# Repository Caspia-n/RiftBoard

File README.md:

<h1>My Project</h1>
RiftBoard is a comprehensive devboard built around the RP2040 chipset, it features a very fancy (and time consuming) ground fill, some 3v3 and some VBUS, also lots of GND. I built it mainly for testing and using sensors and actuators, either on their own or working together.
<h1>Why?</h1>
I started this project because I wanted to get into hardware design and embedded electronics. But also because I love HackClub and what they do and really wanted to be a part of this, I thank you so much for the opportunities, and I also really want a hot plate for future projects :).

<h1>Pics</h1>

<h1>BOM</h1>
<table>
    <tr>
        <td>Mrf#</td>
        <td>Mfr.</td>
        <td>Order Qty.</td>
        <td>Unit Price(USD)</td>
        <td>Ext.Price(USD)</td>
        <td>LCSC#</td>
        <td>Package</td>
        <td>Min</td>
        <td>Mult</td>
        <td>SPQ</td>
        <td>Availability</td>
        <td>Stock Status</td>
        <td>Customer Notes</td>
        <td>Description</td>
        <td>Purpose</td>
        <td>Product Link</td>
    </tr>
    <tr>
        <td>CC0402KRX7R7BB104</td>
        <td>YAGEO</td>
        <td>100</td>
        <td>0.0010</td>
        <td>0.10</td>
        <td>C60474</td>
        <td>0402</td>
        <td>100</td>
        <td>100</td>
        <td>10000</td>
        <td>11898300</td>
        <td>In Stock</td>
        <td></td>
        <td>100nF ±10% 16V Ceramic Capacitor X7R 0402</td>
        <td>Capacitors for decoupling and stabilisation of powerlines</td>
        <td>https://www.lcsc.com/product-detail/C60474.html</td>
    </tr>
    <tr>
        <td>CL05A105KP5NNNC</td>
        <td>Samsung Electro-Mechanics</td>
        <td>100</td>
        <td>0.0023</td>
        <td>0.23</td>
        <td>C14445</td>
        <td>0402</td>
        <td>100</td>
        <td>100</td>
        <td>10000</td>
        <td>1500800</td>
        <td>In Stock</td>
        <td></td>
        <td>1uF ±10% 10V Ceramic Capacitor X5R 0402</td>
        <td>One for each power line</td>
        <td>https://www.lcsc.com/product-detail/C14445.html</td>
    </tr>
    <tr>
        <td>CL10A106KP8NNNC</td>
        <td>Samsung Electro-Mechanics</td>
        <td>50</td>
        <td>0.0080</td>
        <td>0.40</td>
        <td>C19702</td>
        <td>0603</td>
        <td>50</td>
        <td>50</td>
        <td>4000</td>
        <td>3665250</td>
        <td>In Stock</td>
        <td></td>
        <td>10uF ±10% 10V Ceramic Capacitor X5R 0603</td>
        <td>Caps for the stepdown converter</td>
        <td>https://www.lcsc.com/product-detail/C19702.html</td>
    </tr>
    <tr>
        <td>CL05C330JB5NNNC</td>
        <td>Samsung Electro-Mechanics</td>
        <td>100</td>
        <td>0.0036</td>
        <td>0.36</td>
        <td>C70465</td>
        <td>0402</td>
        <td>100</td>
        <td>100</td>
        <td>10000</td>
        <td>209500</td>
        <td>In Stock</td>
        <td></td>
        <td>33pF ±5% 50V Ceramic Capacitor C0G 0402</td>
        <td>Caps for the crystal</td>
        <td>https://www.lcsc.com/product-detail/C70465.html</td>
    </tr>
    <tr>
        <td>YLED0603B</td>
        <td>YONGYUTAI</td>
        <td>100</td>
        <td>0.0060</td>
        <td>0.60</td>
        <td>C19171394</td>
        <td>0603</td>
        <td>100</td>
        <td>100</td>
        <td>4000</td>
        <td>55000</td>
        <td>In Stock</td>
        <td></td>
        <td>Blue LED Indication - Discrete 2.6V~3.2V 0603</td>
        <td>Blue programmable LED</td>
        <td>https://www.lcsc.com/product-detail/C19171394.html</td>
    </tr>
    <tr>
        <td>YLED0603R</td>
        <td>YONGYUTAI</td>
        <td>100</td>
        <td>0.0061</td>
        <td>0.61</td>
        <td>C19171390</td>
        <td>0603</td>
        <td>100</td>
        <td>100</td>
        <td>4000</td>
        <td>267100</td>
        <td>In Stock</td>
        <td></td>
        <td>Red LED Indication - Discrete 1.8V~2.4V 0603</td>
        <td>Red programmable LED</td>
        <td>https://www.lcsc.com/product-detail/C19171390.html</td>
    </tr>
    <tr>
        <td>HX TYPE-C 16PIN</td>
        <td>hanxia</td>
        <td>5</td>
        <td>0.0704</td>
        <td>0.35</td>
        <td>C5178539</td>
        <td>SMD</td>
        <td>5</td>
        <td>5</td>
        <td>1000</td>
        <td>34690</td>
        <td>In Stock</td>
        <td></td>
        <td>USB-C (USB TYPE-C) Receptacle Connector 16 Position Surface Mount, Right Angle</td>
        <td>Usb interface</td>
        <td>https://www.lcsc.com/product-detail/C5178539.html</td>
    </tr>
    <tr>
        <td>PH2.54-1X20P-H25</td>
        <td>JXTCONN</td>
        <td>10</td>
        <td>0.0920</td>
        <td>0.92</td>
        <td>C42431804</td>
        <td>Through Hole,P=2.54mm</td>
        <td>5</td>
        <td>5</td>
        <td>200</td>
        <td>9870</td>
        <td>In Stock</td>
        <td></td>
        <td>Pin Header 20 Position 2.54mm Pitch Single Row Through Hole -40℃~+105℃</td>
        <td>Main Pin headers</td>
        <td>https://www.lcsc.com/product-detail/C42431804.html</td>
    </tr>
    <tr>
        <td>HX PH254-01-03-Z-L11.5 pcb pin header</td>
        <td>hanxia</td>
        <td>20</td>
        <td>0.0192</td>
        <td>0.38</td>
        <td>C52016391</td>
        <td>Through Hole,P=2.54mm</td>
        <td>20</td>
        <td>20</td>
        <td>2000</td>
        <td>9760</td>
        <td>In Stock</td>
        <td></td>
        <td>Pin Header 1 2.5mm 6mm 3P -40℃~+105℃ 3mm 2.54mm 3A 1kV 1x3P Through Hole,P=2.54mm Headers, Male Pins RoHS</td>
        <td>3pin-connector</td>
        <td>https://www.lcsc.com/product-detail/C52016391.html</td>
    </tr>
    <tr>
        <td>RC0402FR-075K1L</td>
        <td>YAGEO</td>
        <td>100</td>
        <td>0.0009</td>
        <td>0.09</td>
        <td>C105872</td>
        <td>0402</td>
        <td>100</td>
        <td>100</td>
        <td>10000</td>
        <td>1024700</td>
        <td>In Stock</td>
        <td></td>
        <td>5.1kΩ 62.5mW 50V Thick Film Resistor ±100ppm/℃ ±1% 0402 Chip Resistor - Surface Mount RoHS</td>
        <td>Pull-down resistors for CC1/2 on usb interface</td>
        <td>https://www.lcsc.com/product-detail/C105872.html</td>
    </tr>
    <tr>
        <td>FRC0402F27R0TS</td>
        <td>FOJAN</td>
        <td>100</td>
        <td>0.0006</td>
        <td>0.06</td>
        <td>C2909343</td>
        <td>0402</td>
        <td>100</td>
        <td>100</td>
        <td>10000</td>
        <td>443300</td>
        <td>In Stock</td>
        <td></td>
        <td>27Ω ±1% 62.5mW 0402 Thick Film Resistor</td>
        <td>Resistors for the differential pair to usb interface</td>
        <td>https://www.lcsc.com/product-detail/C2909343.html</td>
    </tr>
    <tr>
        <td>RC0402FR-071KL</td>
        <td>YAGEO</td>
        <td>100</td>
        <td>0.0008</td>
        <td>0.08</td>
        <td>C106235</td>
        <td>0402</td>
        <td>100</td>
        <td>100</td>
        <td>10000</td>
        <td>5051800</td>
        <td>In Stock</td>
        <td></td>
        <td>1kΩ 62.5mW 50V Thick Film Resistor ±100ppm/℃ ±1% 0402 Chip Resistor - Surface Mount RoHS</td>
        <td>One for the crystal and one for flash mem</td>
        <td>https://www.lcsc.com/product-detail/C106235.html</td>
    </tr>
    <tr>
        <td>RC0402FR-0710KL</td>
        <td>YAGEO</td>
        <td>100</td>
        <td>0.0008</td>
        <td>0.08</td>
        <td>C60490</td>
        <td>0402</td>
        <td>100</td>
        <td>100</td>
        <td>10000</td>
        <td>1433400</td>
        <td>In Stock</td>
        <td></td>
        <td>62.5mW 10kΩ 50V Thick Film Resistor ±100ppm/℃ ±1% 0402 Chip Resistor - Surface Mount RoHS</td>
        <td>Flash mem to power resistor</td>
        <td>https://www.lcsc.com/product-detail/C60490.html</td>
    </tr>
    <tr>
        <td>FRC0402F50R0TS</td>
        <td>FOJAN</td>
        <td>100</td>
        <td>0.0006</td>
        <td>0.06</td>
        <td>C51048227</td>
        <td>0402</td>
        <td>100</td>
        <td>100</td>
        <td>10000</td>
        <td>495800</td>
        <td>In Stock</td>
        <td></td>
        <td>62.5mW 50Ω 50V Thick Film Resistor ±100ppm/℃ ±1% 0402 Chip Resistor - Surface Mount RoHS</td>
        <td>50R resistor for Red LED</td>
        <td>https://www.lcsc.com/product-detail/C51048227.html</td>
    </tr>
    <tr>
        <td>0603WAF100JT5E</td>
        <td>UNI-ROYAL</td>
        <td>20</td>
        <td>0.0017</td>
        <td>0.03</td>
        <td>C22859</td>
        <td>0603</td>
        <td>20</td>
        <td>20</td>
        <td>5000</td>
        <td>158680</td>
        <td>In Stock</td>
        <td></td>
        <td>10Ω ±1% 100mW 0603 Thick Film Resistor</td>
        <td>10R resistor for Blue LED</td>
        <td>https://www.lcsc.com/product-detail/C22859.html</td>
    </tr>
    <tr>
        <td>TS-1088-AR02016</td>
        <td>XUNPU</td>
        <td>10</td>
        <td>0.0545</td>
        <td>0.55</td>
        <td>C720477</td>
        <td>SMD,4x3mm</td>
        <td>10</td>
        <td>10</td>
        <td>4000</td>
        <td>376970</td>
        <td>In Stock</td>
        <td></td>
        <td>Tactile Switch SPST 160gf 2mm SMD (SMT) Tab 4mm x 3mm Surface Mount</td>
        <td>One switch for flash write mode, and one programmable.</td>
        <td>https://www.lcsc.com/product-detail/C720477.html</td>
    </tr>
    <tr>
        <td>RP2040</td>
        <td>Raspberry Pi</td>
        <td>5</td>
        <td>0.9482</td>
        <td>4.74</td>
        <td>C2040</td>
        <td>LQFN-56(7x7)</td>
        <td>1</td>
        <td>1</td>
        <td>3400</td>
        <td>101373</td>
        <td>In Stock</td>
        <td></td>
        <td>133MHz 30 LQFN-56(7x7) Microcontrollers RoHS</td>
        <td>The MCU on this board</td>
        <td>https://www.lcsc.com/product-detail/C2040.html</td>
    </tr>
    <tr>
        <td>MCP1700T-3302E/TT</td>
        <td>MICROCHIP</td>
        <td>5</td>
        <td>0.3762</td>
        <td>1.88</td>
        <td>C39051</td>
        <td>SOT-23</td>
        <td>5</td>
        <td>5</td>
        <td>3000</td>
        <td>9370</td>
        <td>In Stock</td>
        <td></td>
        <td>3.3V Positive Fixed SOT-23 Voltage Regulators - Linear, Low Drop Out (LDO) Regulators RoHS</td>
        <td>The stepdown converter from 5v to 3v3</td>
        <td>https://www.lcsc.com/product-detail/C39051.html</td>
    </tr>
    <tr>
        <td>W25Q16JVUXIQ</td>
        <td>Winbond</td>
        <td>10</td>
        <td>1.0529</td>
        <td>10.53</td>
        <td>C2843335</td>
        <td>USON-8-EP(2x3)</td>
        <td>10</td>
        <td>10</td>
        <td>4000</td>
        <td>34380</td>
        <td>In Stock</td>
        <td></td>
        <td>2.7V~3.6V 16Mbit 133MHz SPI USON-8-EP(2x3) Memory (ICs) RoHS</td>
        <td>The flash memory module</td>
        <td>https://www.lcsc.com/product-detail/C2843335.html</td>
    </tr>
    <tr>
        <td>X322512MSB4SI</td>
        <td>YXC Crystal Oscillators</td>
        <td>10</td>
        <td>0.0734</td>
        <td>0.73</td>
        <td>C9002</td>
        <td>SMD3225-4P</td>
        <td>10</td>
        <td>10</td>
        <td>3000</td>
        <td>436800</td>
        <td>In Stock</td>
        <td></td>
        <td>Crystal 12MHz ±10ppm 20pF SMD3225-4P</td>
        <td>the Crystal oscilator</td>
        <td>https://www.lcsc.com/product-detail/C9002.html</td>
    </tr>
</table>

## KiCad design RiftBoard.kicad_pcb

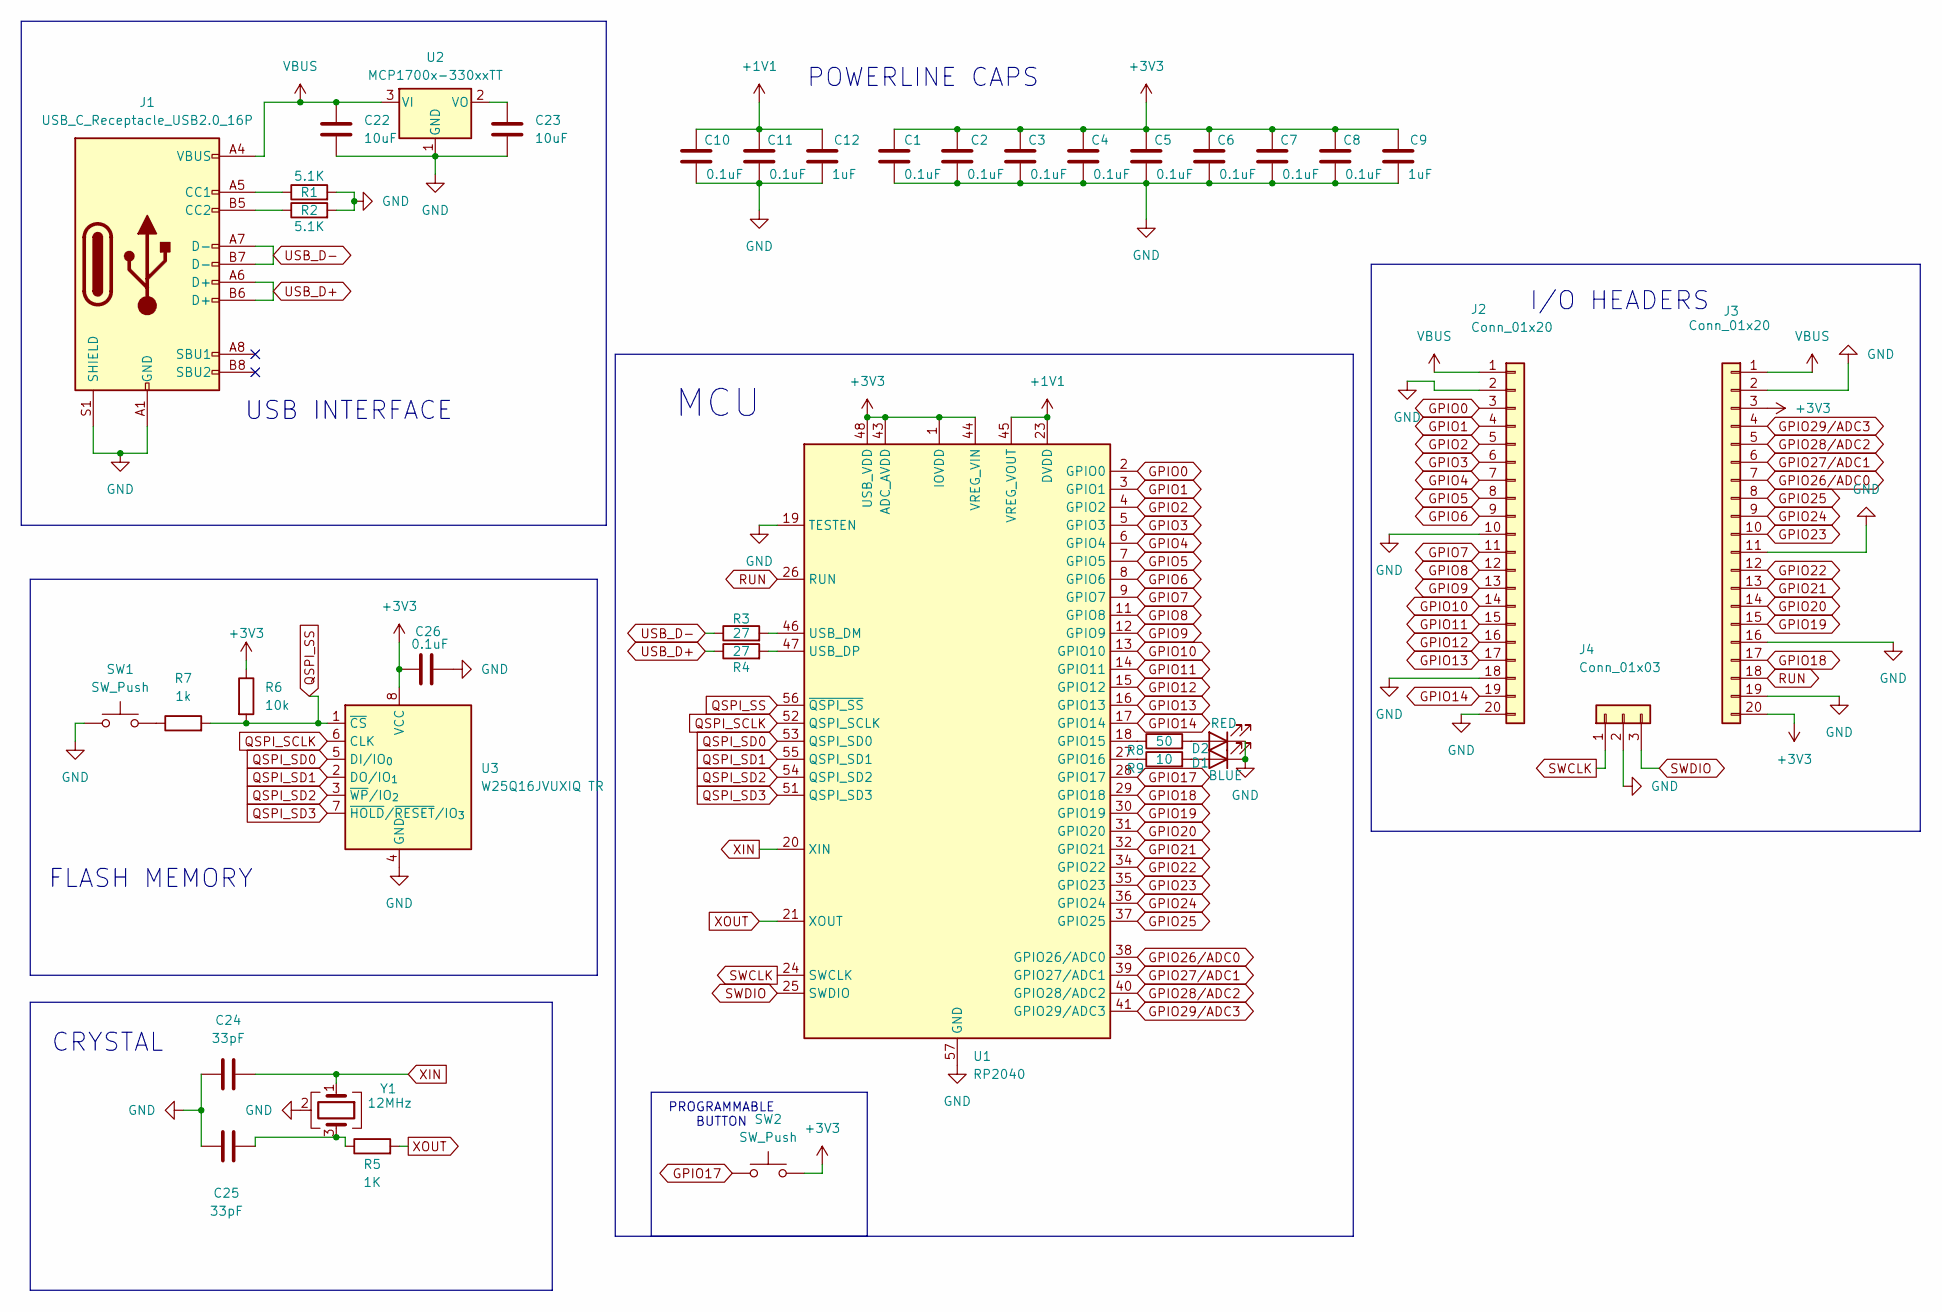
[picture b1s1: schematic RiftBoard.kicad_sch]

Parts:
C1, C2, C3, C4, C5, C6, C7, C8, C10, C11, C26: 0.1uF; C_0402_1005Metric
C9, C12: 1uF; C_0402_1005Metric
C22, C23: 10uF; C_0603_1608Metric
C24, C25: 33pF; C_0402_1005Metric
D1: BLUE; LED_0603_1608Metric
D2: RED; LED_0603_1608Metric
J1: USB_C_Receptacle_USB2.0_16P; USB_C_Receptacle_HRO_TYPE-C-31-M-12
J2, J3: Conn_01x20; PinHeader_1x20_P2.54mm_Vertical
J4: Conn_01x03; PinHeader_1x03_P2.54mm_Vertical
R1, R2: 5.1K; R_0402_1005Metric
R3, R4: 27; R_0402_1005Metric
R5: 1K; R_0402_1005Metric
R6: 10k; R_0402_1005Metric
R7: 1k; R_0402_1005Metric
R8: 50; R_0402_1005Metric
R9: 10; R_0402_1005Metric
SW1, SW2: SW_Push; SW_Push_SPST_NO_Alps_SKRK
U1: RP2040; QFN-56-1EP_7x7mm_P0.4mm_EP3.2x3.2mm
U2: MCP1700x-330xxTT; SOT-23
U3: W25Q16JVUXIQ TR; Winbond_USON-8-1EP_3x2mm_P0.5mm_EP0.2x1.6mm
Y1: 12MHz; Crystal_SMD_3225-4Pin_3.2x2.5mm

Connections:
+1V1: C10.1, C11.1, C12.1, U1.23 (DVDD), U1.45 (VREG_VOUT), U1.50 (DVDD)
+3V3: C1.1, C2.1, C3.1, C4.1, C5.1, C6.1, C7.1, C8.1, C9.1, C26.1, J3.3, J3.20, R6.1, SW2.2, U1.1 (IOVDD), U1.10 (IOVDD), U1.22 (IOVDD), U1.33 (IOVDD), U1.42 (IOVDD), U1.43 (ADC_AVDD), U1.44 (VREG_VIN), U1.48 (USB_VDD), U1.49 (IOVDD), U3.8 (VCC)
GND: C1.2, C2.2, C3.2, C4.2, C5.2, C6.2, C7.2, C8.2, C9.2, C10.2, C11.2, C12.2, C22.2, C23.2, C24.1, C25.1, C26.2, D1.1 (K), D2.1 (K), J1.A1 (GND), J1.A12 (GND), J1.B1 (GND), J1.B12 (GND), J1.S1 (SHIELD), J1.SH (SHIELD), J2.2, J2.10, J2.18, J2.20, J3.2, J3.11, J3.16, J3.19, J4.2, R1.2, R2.2, SW1.1, U1.19 (TESTEN), U1.57 (GND), U2.1 (GND), U3.4 (GND), Y1.2 (G), Y1.4 (G)
GPIO0: J2.3, U1.2 (GPIO0)
GPIO1: J2.4, U1.3 (GPIO1)
GPIO2: J2.5, U1.4 (GPIO2)
GPIO3: J2.6, U1.5 (GPIO3)
GPIO4: J2.7, U1.6 (GPIO4)
GPIO5: J2.8, U1.7 (GPIO5)
GPIO6: J2.9, U1.8 (GPIO6)
GPIO7: J2.11, U1.9 (GPIO7)
GPIO8: J2.12, U1.11 (GPIO8)
GPIO9: J2.13, U1.12 (GPIO9)
GPIO10: J2.14, U1.13 (GPIO10)
GPIO11: J2.15, U1.14 (GPIO11)
GPIO12: J2.16, U1.15 (GPIO12)
GPIO13: J2.17, U1.16 (GPIO13)
GPIO14: J2.19, U1.17 (GPIO14)
GPIO17: SW2.1, U1.28 (GPIO17)
GPIO18: J3.17, U1.29 (GPIO18)
GPIO19: J3.15, U1.30 (GPIO19)
GPIO20: J3.14, U1.31 (GPIO20)
GPIO21: J3.13, U1.32 (GPIO21)
GPIO22: J3.12, U1.34 (GPIO22)
GPIO23: J3.10, U1.35 (GPIO23)
GPIO24: J3.9, U1.36 (GPIO24)
GPIO25: J3.8, U1.37 (GPIO25)
GPIO26/ADC0: J3.7, U1.38 (GPIO26/ADC0)
GPIO27/ADC1: J3.6, U1.39 (GPIO27/ADC1)
GPIO28/ADC2: J3.5, U1.40 (GPIO28/ADC2)
GPIO29/ADC3: J3.4, U1.41 (GPIO29/ADC3)
unnamed: C25.2, R5.1, Y1.3
unnamed: D1.2 (A), R9.2
unnamed: D2.2 (A), R8.2
unnamed: J1.A5 (CC1), R1.1
unnamed: J1.B5 (CC2), R2.1
unnamed: R7.1, SW1.2
unnamed: R8.1, U1.18 (GPIO15)
unnamed: R9.1, U1.27 (GPIO16)
unnamed: R3.2, U1.46 (USB_DM)
unnamed: R4.2, U1.47 (USB_DP)
unnamed: C23.1, U2.2 (VO)
QSPI_SCLK: U1.52 (QSPI_SCLK), U3.6 (CLK)
QSPI_SD0: U1.53 (QSPI_SD0), U3.5 (DI/IO_{0})
QSPI_SD1: U1.55 (QSPI_SD1), U3.2 (DO/IO_{1})
QSPI_SD2: U1.54 (QSPI_SD2), U3.3 (~WP/IO_{2})
QSPI_SD3: U1.51 (QSPI_SD3), U3.7 (~HOLD/~RESET/IO_{3})
QSPI_SS: R6.2, R7.2, U1.56 (~QSPI_SS), U3.1 (~CS)
RUN: J3.18, U1.26 (RUN)
SWCLK: J4.1, U1.24 (SWCLK)
SWDIO: J4.3, U1.25 (SWDIO)
USB_D+: J1.A6 (D+), J1.B6 (D+), R4.1
USB_D-: J1.A7 (D-), J1.B7 (D-), R3.1
VBUS: C22.1, J1.A4 (VBUS), J1.A9 (VBUS), J1.B4 (VBUS), J1.B9 (VBUS), J2.1, J3.1, U2.3 (VI)
XIN: C24.2, U1.20 (XIN), Y1.1
XOUT: R5.2, U1.21 (XOUT)

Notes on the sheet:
POWERLINE CAPS
CRYSTAL
USB INTERFACE
I/O HEADERS
FLASH MEMORY
MCU
PROGRAMMABLE BUTTON

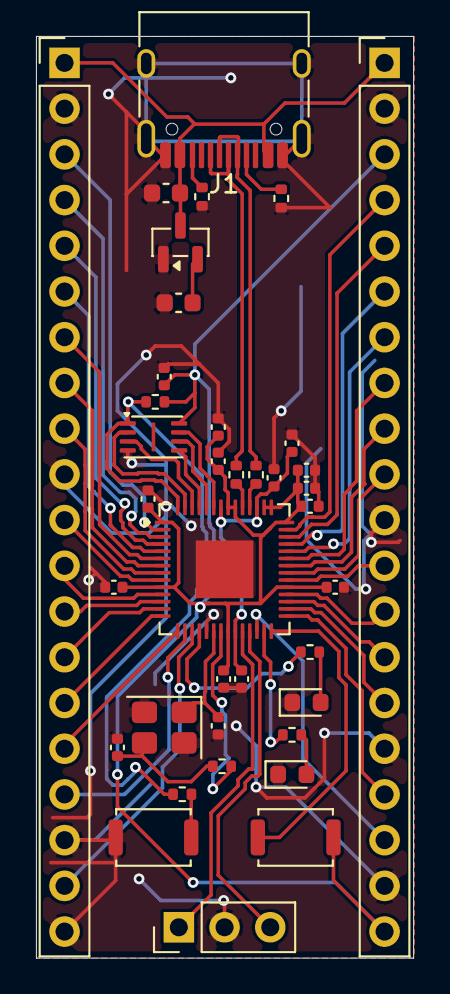
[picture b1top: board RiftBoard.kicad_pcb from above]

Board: 2 copper layers, 21.0 x 51.2 mm, 38 parts (0 on the bottom side), 56 nets.

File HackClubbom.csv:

Designator,Footprint,Quantity,Value,LCSC Part #
"C1, C10, C11, C2, C26, C3, C4, C5, C6, C7, C8",0402,11,0.1uF,
"C12, C9",0402,2,1uF,
"C22, C23",0603,2,10uF,
"C24, C25",0402,2,33pF,
D1,0603,1,BLUE,
D2,0603,1,RED,
J1,USB_C_Receptacle_HRO_TYPE-C-31-M-12,1,USB_C_Receptacle_USB2.0_16P,
"J2, J3",PinHeader_1x20_P2.54mm_Vertical,2,Conn_01x20,
J4,PinHeader_1x03_P2.54mm_Vertical,1,Conn_01x03,
"R1, R2",0402,2,5.1K,
"R3, R4",0402,2,27,
"R5, R7",0402,2,1K,
R6,0402,1,10k,
R8,0402,1,50,
R9,0402,1,10,
"SW1, SW2",SW_Push_SPST_NO_Alps_SKRK,2,SW_Push,
U1,QFN-56-1EP_7x7mm_P0.4mm_EP3.2x3.2mm,1,RP2040,
U2,SOT-23,1,MCP1700x-330xxTT,
U3,Winbond_USON-8-1EP_3x2mm_P0.5mm_EP0.2x1.6mm,1,W25Q16JVUXIQ TR,
Y1,Crystal_SMD_3225-4Pin_3.2x2.5mm,1,12MHz,

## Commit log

2026-04-06 Project Init
2026-04-07 10:19 logoff
    Decoupling caps, and differential data line done
2026-04-07 Pre-routing
2026-04-07 Failed to trace without swapping gpio around, Im going to flip pin header for better compatibility with rp2040.
2026-04-08 Finished PCB stuffs, now just design and I can move on to the production and assembly.
2026-04-10 submission
2026-04-10 Document schematic and PCB design progress in README
2026-04-10 Revise README with project overview and BOM
    Updated the README to include project details, BOM, and images.
2026-04-10 Replace BOM and remove gerber/placement files
    Remove legacy BOM and Gerber/placement exports and add a new LCSC-ready BOM. Deleted: HackClubbom.csv, gerber_to_order/RiftBoard-top-pos.csv, gerber_to_order/RiftBoard-bottom-pos.csv, and gerber_to_o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
2026-04-10 Fix HTML tags in README.md
2026-04-11 Step file added
2026-05-05 Hopefully final fix
